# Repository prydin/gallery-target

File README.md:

# Shooting Gallery Target
Custom made shooting gallery target

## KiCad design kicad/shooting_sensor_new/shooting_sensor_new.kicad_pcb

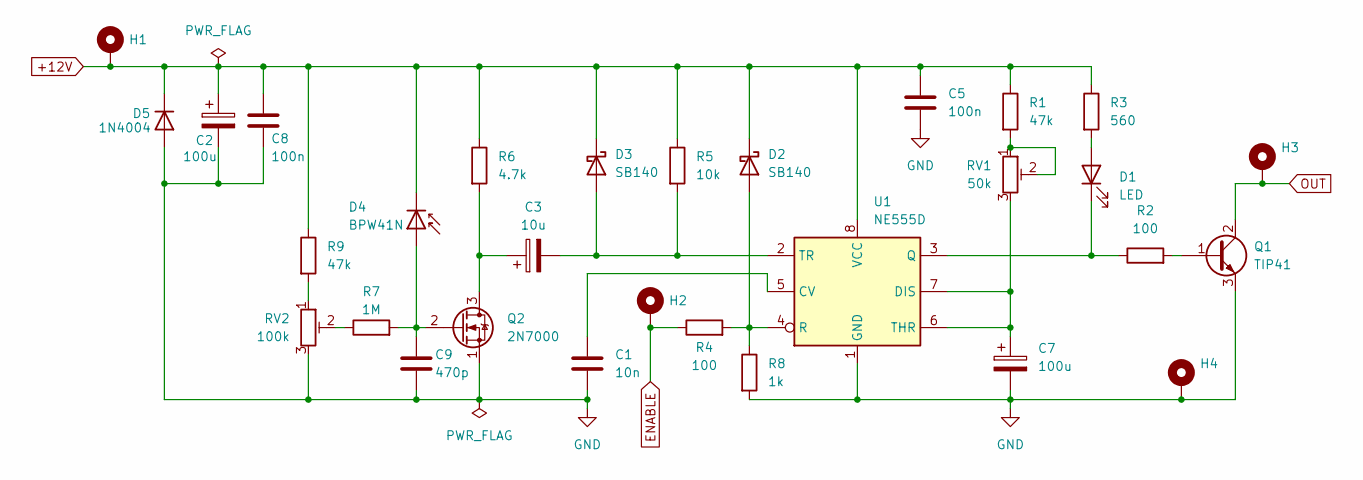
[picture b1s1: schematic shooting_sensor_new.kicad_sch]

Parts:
C1: 10n; C_Disc_D3.0mm_W1.6mm_P2.50mm
C2, C7: 100u; CP_Radial_D4.0mm_P2.00mm
C3: 10u; CP_Radial_D4.0mm_P2.00mm
C5, C8: 100n; C_Disc_D3.0mm_W1.6mm_P2.50mm
C9: 470p; C_Disc_D3.0mm_W1.6mm_P2.50mm
D1: LED; LED_D5.0mm_Horizontal_O6.35mm_Z15.0mm
D2, D3: SB140; D_DO-41_SOD81_P7.62mm_Horizontal
D4: BPW41N; Osram_SFH225
D5: 1N4004; D_DO-41_SOD81_P7.62mm_Horizontal
H1, H2: MountingHole_Pad; TestPoint_Loop_D2.54mm_Drill1.5mm_Beaded
H3, H4: OUT; TestPoint_Loop_D2.54mm_Drill1.5mm_Beaded
Q1: TIP41; TO-220-3_Vertical
Q2: 2N7000; TO-92_Inline
R1, R9: 47k; R_Axial_DIN0207_L6.3mm_D2.5mm_P2.54mm_Vertical
R2, R4: 100; R_Axial_DIN0207_L6.3mm_D2.5mm_P2.54mm_Vertical
R3: 560; R_Axial_DIN0207_L6.3mm_D2.5mm_P7.62mm_Horizontal
R5: 10k; R_Axial_DIN0207_L6.3mm_D2.5mm_P2.54mm_Vertical
R6: 4.7k; R_Axial_DIN0207_L6.3mm_D2.5mm_P2.54mm_Vertical
R7: 1M; R_Axial_DIN0207_L6.3mm_D2.5mm_P2.54mm_Vertical
R8: 1k; R_Axial_DIN0207_L6.3mm_D2.5mm_P2.54mm_Vertical
RV1: 50k; Potentiometer_Piher_PT-6-H_Horizontal
RV2: 100k; Potentiometer_Vishay_T73YP_Vertical
U1: NE555D; DIP-8_W7.62mm

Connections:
+12V: C2.1, C5.1, C8.1, D2.1 (K), D3.1 (K), D4.1 (K), D5.1 (K), H1.1, R1.1, R3.1, R5.1, R6.1, R9.1, U1.8 (VCC)
ENABLE: H2.1, R4.1
GND: C1.2, C2.2, C5.2, C7.2, C8.2, C9.2, D5.2 (A), H4.1, Q1.3 (E), Q2.1 (S), R8.2, RV2.3, U1.1 (GND); also elsewhere on the board
unnamed: D1.2 (A), R3.2
unnamed: D1.1 (K), R2.1, U1.3 (Q)
unnamed: D2.2 (A), R4.2, R8.1, U1.4 (R)
unnamed 6: C3.2, D3.2 (A), R5.2, U1.2 (TR); also elsewhere on the board
unnamed 7: C9.1, D4.2 (A), Q2.2 (G), R7.2; also elsewhere on the board
unnamed: Q1.1 (B), R2.2
unnamed: C3.1, Q2.3 (D), R6.2
unnamed: R1.2, RV1.1, RV1.2
unnamed: R7.1, RV2.2
unnamed: R9.2, RV2.1
unnamed: C1.1, U1.5 (CV)
unnamed: C7.1, RV1.3, U1.6 (THR), U1.7 (DIS)
OUT: H3.1, Q1.2 (C)

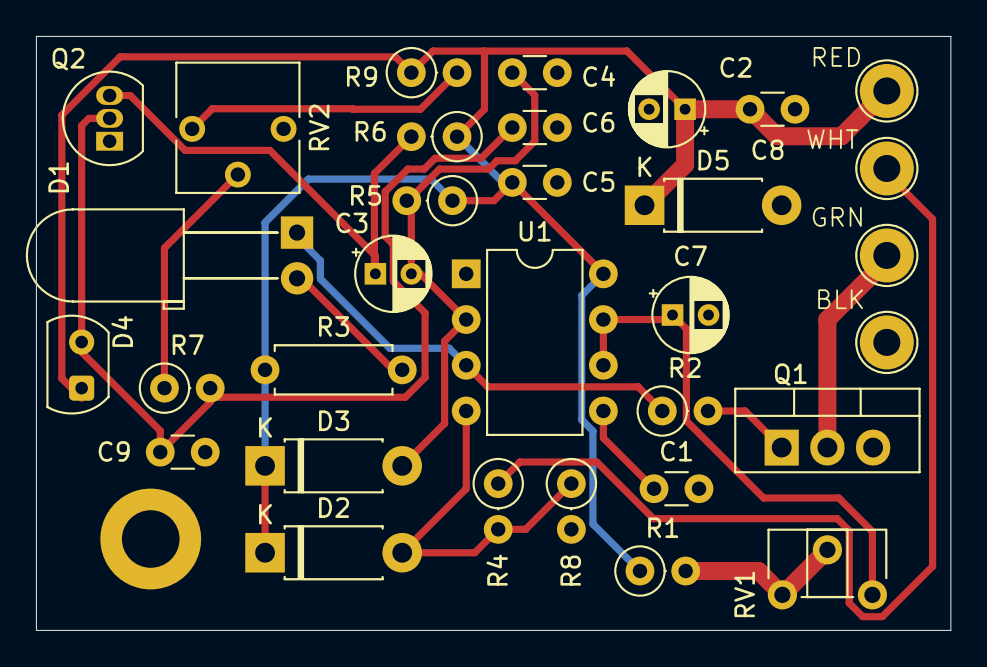
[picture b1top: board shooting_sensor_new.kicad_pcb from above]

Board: 2 copper layers, 50.8 x 33.0 mm, 32 parts (0 on the bottom side), 16 nets.

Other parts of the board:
C4: 10n; C_Disc_D3.0mm_W1.6mm_P2.50mm
C6: 1n; C_Disc_D3.0mm_W1.6mm_P2.50mm

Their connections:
GND: C4.2, C6.2; also elsewhere on the board
unnamed 6: C4.1; also elsewhere on the board
unnamed 7: C6.1; also elsewhere on the board

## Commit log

2024-12-08 Added KiCAD and SPICE files
2024-12-08 Added Gerber files
